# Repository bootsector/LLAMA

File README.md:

**LLAMA - Low Lag Amazing MiSTer Adapter**

This is an open-source / open-hardware controllers adapter for MiSTer FPGA.

Supported outputs are both USB (XInput) and MiSTer's [LLAPI](https://github.com/Kitrinx/LLAPI/blob/master/LLIO.sv) interface.

32U4 module designs include gerber files and SeeedStudio BOM file for Fusion
PCB Assembly service.

LLAMA currently supports original controllers for the systems below:

- Neo Geo / Neo Geo CD (**NOT compatible with SuperGun DB15 based controllers** )
- Super NES
- NES
- TurboGrafx-16 / PC Engine
- Sega Saturn
- Sega Genesis / Master System / Atari 2600 and compatibles

**Latency Measurements - 1000Hz USB polling mode**
| Controller | Samples | Average | Max     | Min   | Std Dev |
| ---------- | ------- | ------- | --------| ----- | ------- |
| LLAMA USB  | 2000    |1.6996ms |2.224ms  |1.188ms| 0.289ms

**Button Mapping**

It's possible to map buttons for each supported joystick. Button mapping is done
based on an index that maps to buttons of the internal abstract pad 
(XInput-like).

Mapping is fully customized by the user. Planning your mapping can be done with
the help of the mapper/LLAMA Mapping.xlsx spreadsheet. Change the buttons of
the supported pads in the "Input" area by selecting them from list boxes. You
can see how those mappings affect output for XInput (USB) and also LLAPI cores
by checking the "Output" area of the spreadsheet.

After setting the mappings in the spreadsheet, simply use the numbers inside
parenthesis for each button of each controller in the ```<profile>``` section of
the mapper/map.xml file. There are two profiles per controller. You just
apply the numbers at the same order they read from the spreadsheet to the
chosen controller profile.

After finishing the changes inside mapper/map.xml file, run the 
mapper/mapper.py application (tested only on Python 2.7). 

```
cd mapper
python mapper.py
```

You should probably
need to install intelhex package via pip beforehand.

```pip install intelhex```

The above will convert map.xml to a file named map.eep. This should be 
flashed into AVR's EEPROM like this:

```dfu-programmer atmega32u4 flash --eeprom map.eep --force```

Mapping is not mandatory. The firmware will save the defaults to EEPROM by
itself the first time it runs if no valid mapping/config is found.

Each controller has two mapping profiles. Below you can find the button
combination on each controller that will switch mapping profiles:

NeoGeo: Down + Start + B

NES: Down + Start + A

SNES: Down + Start + A

Saturn: Down + Start + C

TG16/PCE: Down + Start + I

Genesis: Down + Start + C

**Licensing:**

- Firmware and bootloader sources are licensed under [GPL-3.0](LICENSE)
- PCBs are licensed under [CC BY-NC-SA 4.0](pcb/LICENSE.txt)

**Disclaimer:**

The firmware source code made available here is an original creation by Bruno 
Freitas. 

The AVR ASM/C implementation of the LLAPI "slave" interface presented here
was created from scratch by Bruno Freitas. MiSTer's LLAPI "master" interface
protocol described [here](https://github.com/Kitrinx/LLAPI/blob/master/LLIO.sv) 
in SystemVerilog has been used as documentation and reference only.

No source code from third parties has been used used by this project.

No reverse-engineering has been done against commercial and non-commercial
products during the development of this project.

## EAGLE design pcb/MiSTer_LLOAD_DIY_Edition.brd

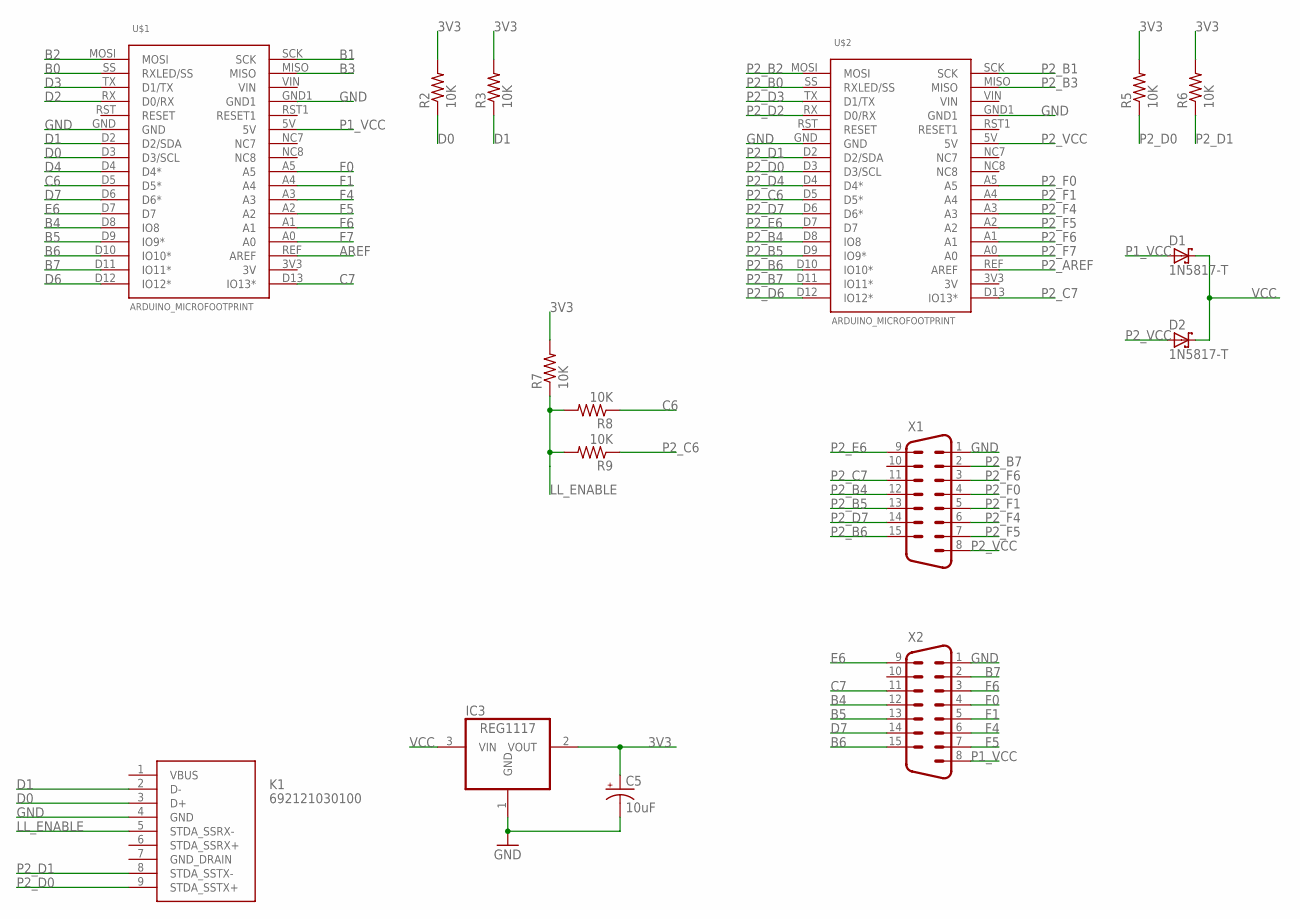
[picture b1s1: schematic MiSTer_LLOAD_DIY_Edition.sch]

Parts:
C5: 10uF; E2,5-6
D1, D2: 1N5817-T; DO41-7.6
IC3: REG1117; SOT223
K1: 692121030100
R2, R3, R5, R6, R7, R8, R9: 10K; 0207/10
U$1, U$2: ARDUINO_MICROFOOTPRINT; ARDUINO-MICRO
X1, X2: M15HP

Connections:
3V3: C5.+, IC3.2 (VOUT), R2.2, R3.2, R5.2, R6.2, R7.2
AREF: U$1.REF (AREF)
B0: U$1.SS (RXLED/SS)
B1: U$1.SCK
B2: U$1.MOSI
B3: U$1.MISO
B4: U$1.D8 (IO8), X2.12
B5: U$1.D9 (IO9*), X2.13
B6: U$1.D10 (IO10*), X2.15
B7: U$1.D11 (IO11*), X2.2
C6: R8.1, U$1.D5 (D5*)
C7: U$1.D13 (IO13*), X2.11
D0: K1.3 (D+), R2.1, U$1.D3 (D3/SCL)
D1: K1.2 (D-), R3.1, U$1.D2 (D2/SDA)
D2: U$1.RX (D0/RX)
D3: U$1.TX (D1/TX)
D4: U$1.D4 (D4*)
D6: U$1.D12 (IO12*)
D7: U$1.D6 (D6*), X2.14
E6: U$1.D7, X2.9
F0: U$1.A5, X2.4
F1: U$1.A4, X2.5
F4: U$1.A3, X2.6
F5: U$1.A2, X2.7
F6: U$1.A1, X2.3
F7: U$1.A0
GND: C5.-, IC3.1 (GND), K1.4 (GND), U$1.GND, U$1.GND1, U$2.GND, U$2.GND1, X1.1, X2.1
LL_ENABLE: K1.5 (STDA_SSRX-), R7.1, R8.2, R9.2
P1_VCC: D1.A, U$1.5V, X2.8
P2_AREF: U$2.REF (AREF)
P2_B0: U$2.SS (RXLED/SS)
P2_B1: U$2.SCK
P2_B2: U$2.MOSI
P2_B3: U$2.MISO
P2_B4: U$2.D8 (IO8), X1.12
P2_B5: U$2.D9 (IO9*), X1.13
P2_B6: U$2.D10 (IO10*), X1.15
P2_B7: U$2.D11 (IO11*), X1.2
P2_C6: R9.1, U$2.D5 (D5*)
P2_C7: U$2.D13 (IO13*), X1.11
P2_D0: K1.9 (STDA_SSTX+), R5.1, U$2.D3 (D3/SCL)
P2_D1: K1.8 (STDA_SSTX-), R6.1, U$2.D2 (D2/SDA)
P2_D2: U$2.RX (D0/RX)
P2_D3: U$2.TX (D1/TX)
P2_D4: U$2.D4 (D4*)
P2_D6: U$2.D12 (IO12*)
P2_D7: U$2.D6 (D6*), X1.14
P2_E6: U$2.D7, X1.9
P2_F0: U$2.A5, X1.4
P2_F1: U$2.A4, X1.5
P2_F4: U$2.A3, X1.6
P2_F5: U$2.A2, X1.7
P2_F6: U$2.A1, X1.3
P2_F7: U$2.A0
P2_VCC: D2.A, U$2.5V, X1.8
VCC: D1.C, D2.C, IC3.3 (VIN)

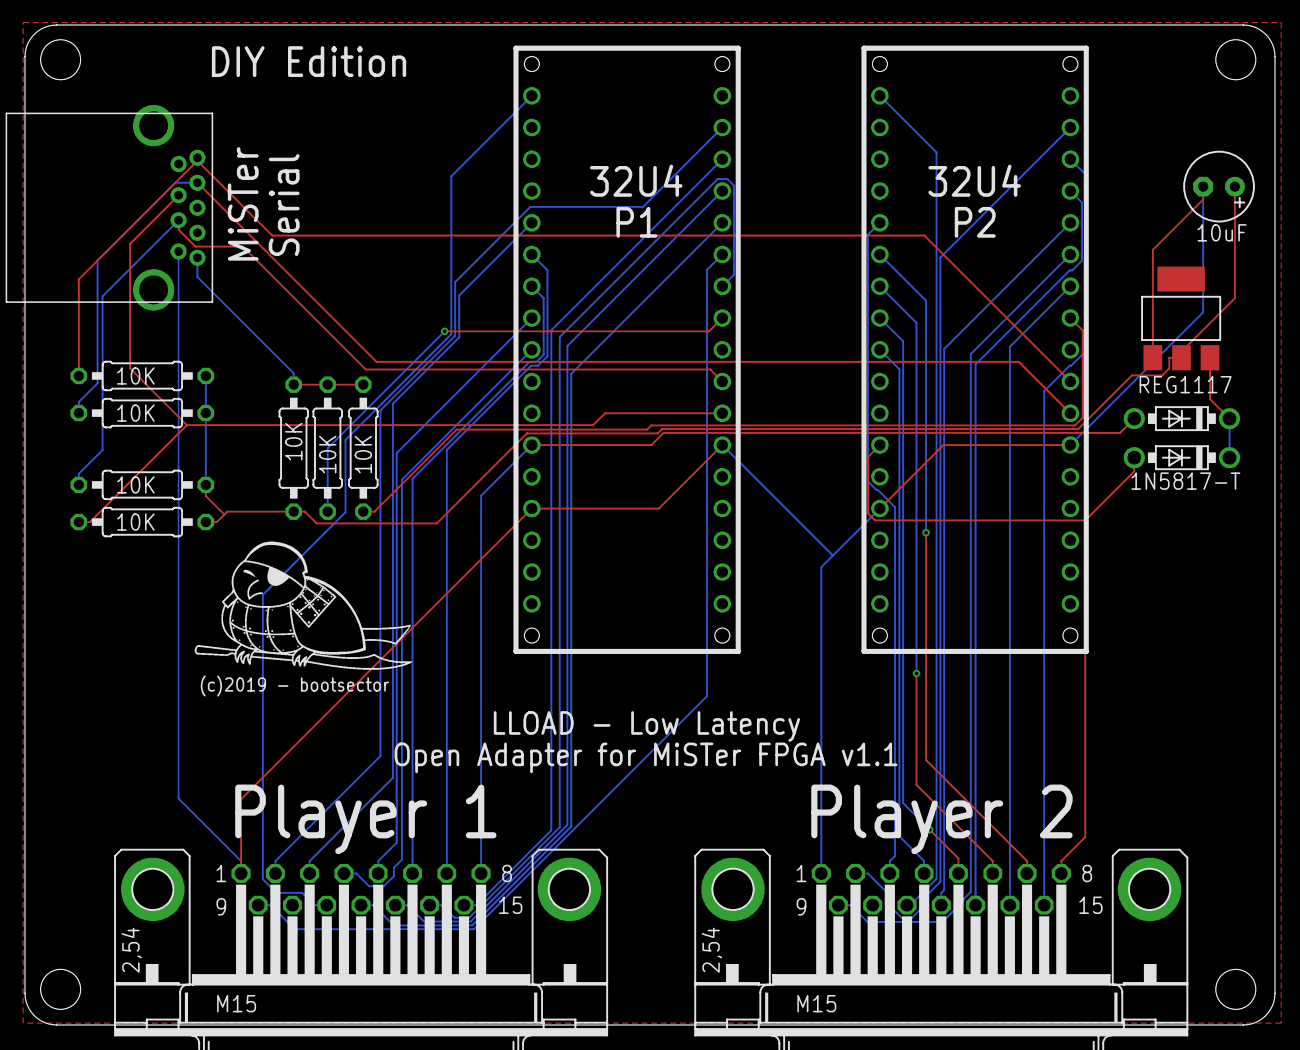
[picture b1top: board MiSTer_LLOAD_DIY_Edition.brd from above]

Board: 2 copper layers, 100.0 x 80.0 mm, 16 parts (0 on the bottom side), 36 nets.

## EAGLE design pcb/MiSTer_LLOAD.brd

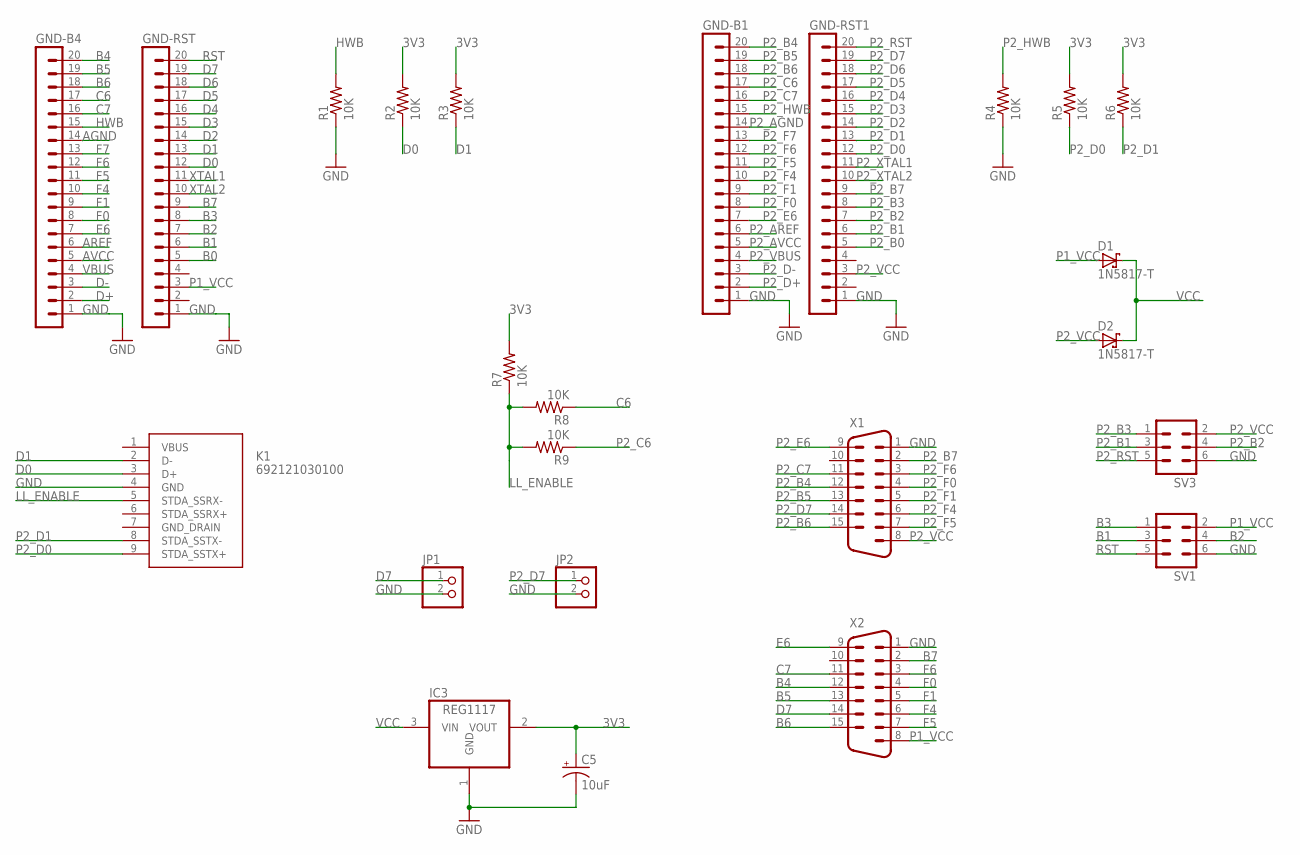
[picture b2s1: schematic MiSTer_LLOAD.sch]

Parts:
C5: 10uF; E2,5-6
D1, D2: 1N5817-T; DO41-7.6
GND-B1, GND-B4: MA20-1
GND-RST, GND-RST1: MA20-1
IC3: REG1117; SOT223
JP1, JP2: PINHD-1X2; 1X02
K1: 692121030100
R1, R2, R3, R4, R5, R6, R7, R8, R9: 10K; 0207/10
SV1, SV3: MA03-2
X1, X2: M15HP

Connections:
3V3: C5.+, IC3.2 (VOUT), R2.2, R3.2, R5.2, R6.2, R7.2
AGND: GND-B4.14
AREF: GND-B4.6
AVCC: GND-B4.5
B0: GND-RST.5
B1: GND-RST.6, SV1.3
B2: GND-RST.7, SV1.4
B3: GND-RST.8, SV1.1
B4: GND-B4.20, X2.12
B5: GND-B4.19, X2.13
B6: GND-B4.18, X2.15
B7: GND-RST.9, X2.2
C6: GND-B4.17, R8.1
C7: GND-B4.16, X2.11
D0: GND-RST.12, K1.3 (D+), R2.1
D1: GND-RST.13, K1.2 (D-), R3.1
D2: GND-RST.14
D3: GND-RST.15
D4: GND-RST.16
D5: GND-RST.17
D6: GND-RST.18
D7: GND-RST.19, JP1.1, X2.14
D+: GND-B4.2
D-: GND-B4.3
E6: GND-B4.7, X2.9
F0: GND-B4.8, X2.4
F1: GND-B4.9, X2.5
F4: GND-B4.10, X2.6
F5: GND-B4.11, X2.7
F6: GND-B4.12, X2.3
F7: GND-B4.13
GND: C5.-, GND-B1.1, GND-B4.1, GND-RST.1, GND-RST1.1, IC3.1 (GND), JP1.2, JP2.2, K1.4 (GND), R1.1, R4.1, SV1.6, SV3.6, X1.1, X2.1
HWB: GND-B4.15, R1.2
LL_ENABLE: K1.5 (STDA_SSRX-), R7.1, R8.2, R9.2
P1_VCC: D1.A, GND-RST.3, SV1.2, X2.8
P2_AGND: GND-B1.14
P2_AREF: GND-B1.6
P2_AVCC: GND-B1.5
P2_B0: GND-RST1.5
P2_B1: GND-RST1.6, SV3.3
P2_B2: GND-RST1.7, SV3.4
P2_B3: GND-RST1.8, SV3.1
P2_B4: GND-B1.20, X1.12
P2_B5: GND-B1.19, X1.13
P2_B6: GND-B1.18, X1.15
P2_B7: GND-RST1.9, X1.2
P2_C6: GND-B1.17, R9.1
P2_C7: GND-B1.16, X1.11
P2_D0: GND-RST1.12, K1.9 (STDA_SSTX+), R5.1
P2_D1: GND-RST1.13, K1.8 (STDA_SSTX-), R6.1
P2_D2: GND-RST1.14
P2_D3: GND-RST1.15
P2_D4: GND-RST1.16
P2_D5: GND-RST1.17
P2_D6: GND-RST1.18
P2_D7: GND-RST1.19, JP2.1, X1.14
P2_D+: GND-B1.2
P2_D-: GND-B1.3
P2_E6: GND-B1.7, X1.9
P2_F0: GND-B1.8, X1.4
P2_F1: GND-B1.9, X1.5
P2_F4: GND-B1.10, X1.6
P2_F5: GND-B1.11, X1.7
P2_F6: GND-B1.12, X1.3
P2_F7: GND-B1.13
P2_HWB: GND-B1.15, R4.2
P2_RST: GND-RST1.20, SV3.5
P2_VBUS: GND-B1.4
P2_VCC: D2.A, GND-RST1.3, SV3.2, X1.8
P2_XTAL1: GND-RST1.11
P2_XTAL2: GND-RST1.10
RST: GND-RST.20, SV1.5
VBUS: GND-B4.4
VCC: D1.C, D2.C, IC3.3 (VIN)
XTAL1: GND-RST.11
XTAL2: GND-RST.10

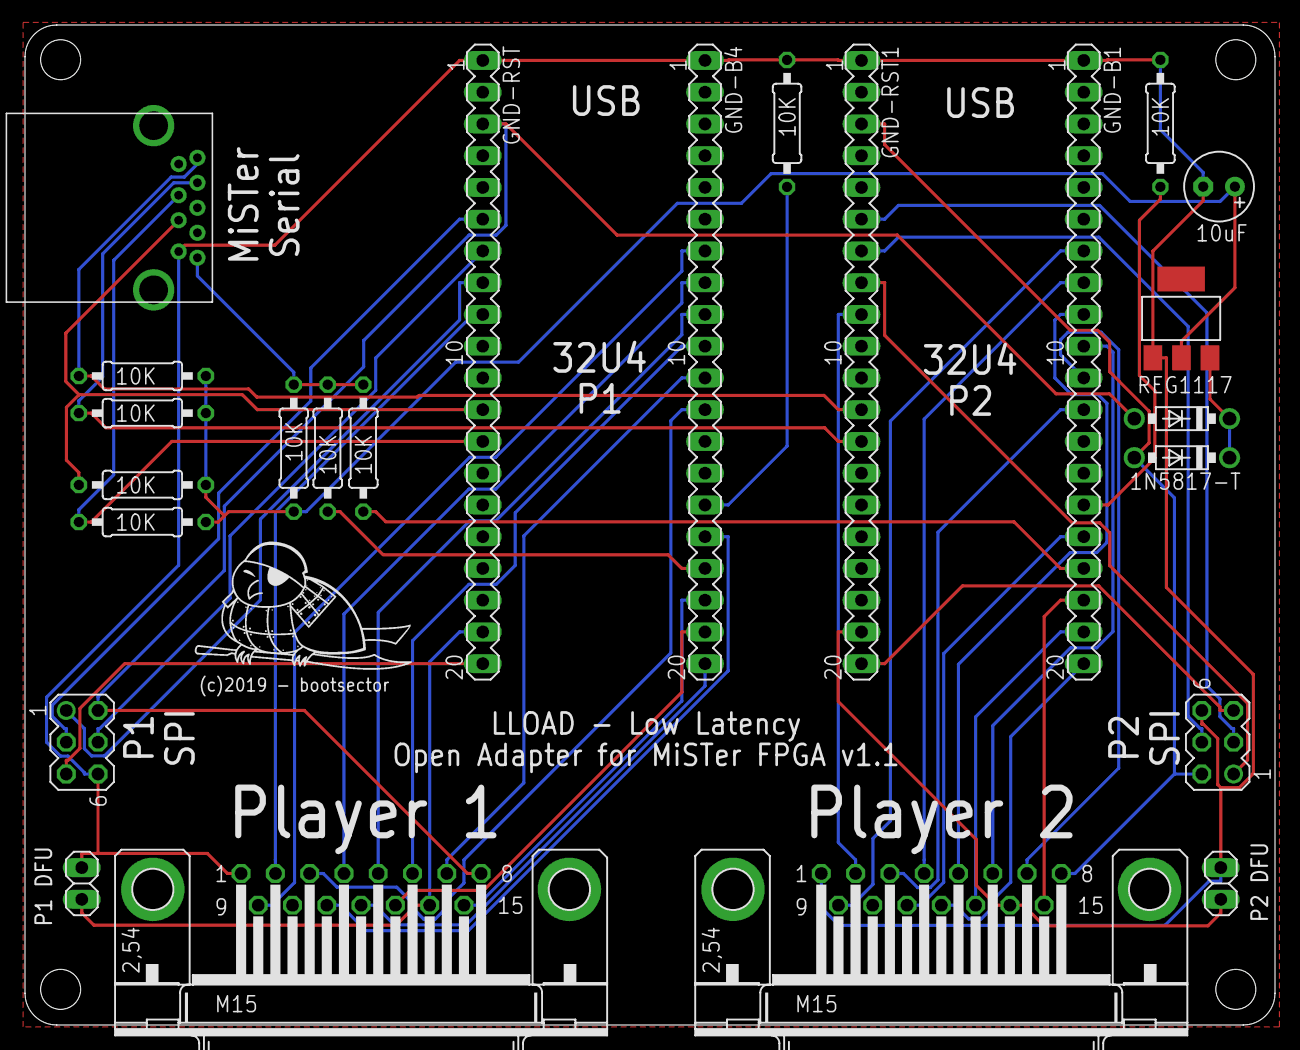
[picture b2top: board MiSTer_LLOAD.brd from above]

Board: 2 copper layers, 100.0 x 80.0 mm, 24 parts (0 on the bottom side), 46 nets.

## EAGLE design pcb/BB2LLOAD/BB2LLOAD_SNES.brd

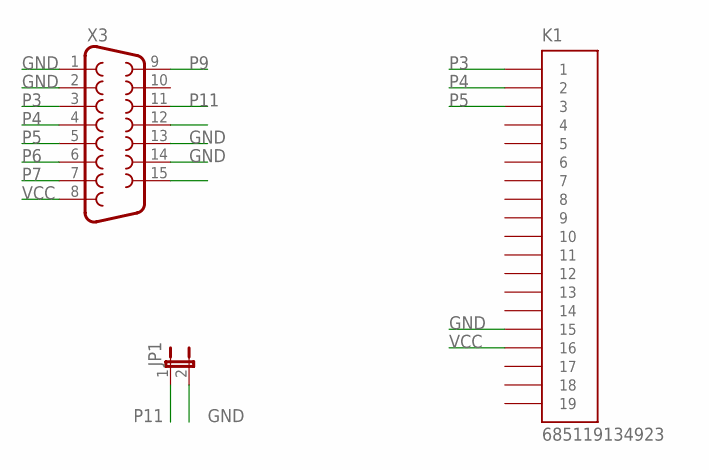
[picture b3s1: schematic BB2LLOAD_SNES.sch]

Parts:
JP1: JP1E; JP1
K1: 685119134923
X3: F15HP

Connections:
GND: JP1.2, K1.15, X3.1, X3.2, X3.13, X3.14
P3: K1.1, X3.3
P4: K1.2, X3.4
P5: K1.3, X3.5
P6: X3.6
P7: X3.7
P9: X3.9
P11: JP1.1, X3.11
VCC: K1.16, X3.8

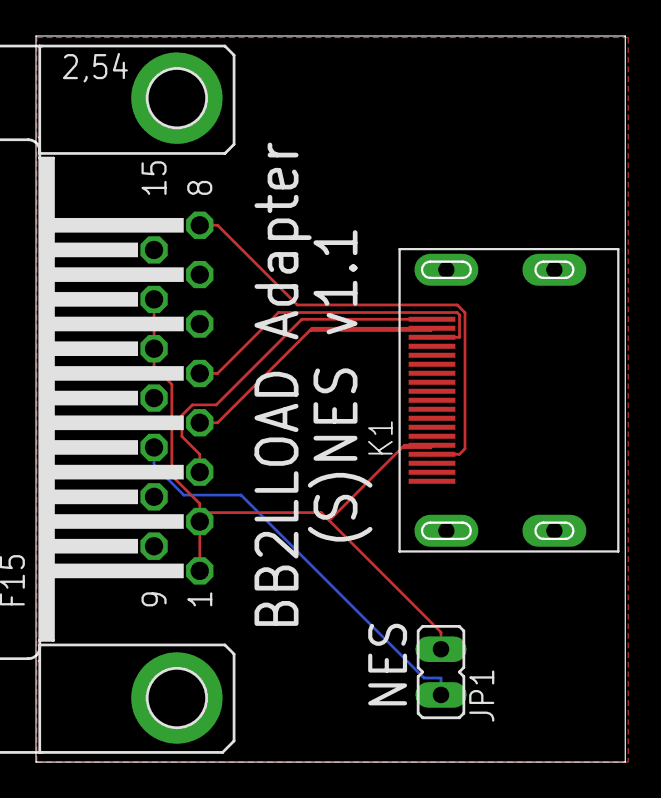
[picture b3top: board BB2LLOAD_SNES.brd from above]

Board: 2 copper layers, 32.6 x 40.2 mm, 3 parts (0 on the bottom side), 6 nets.

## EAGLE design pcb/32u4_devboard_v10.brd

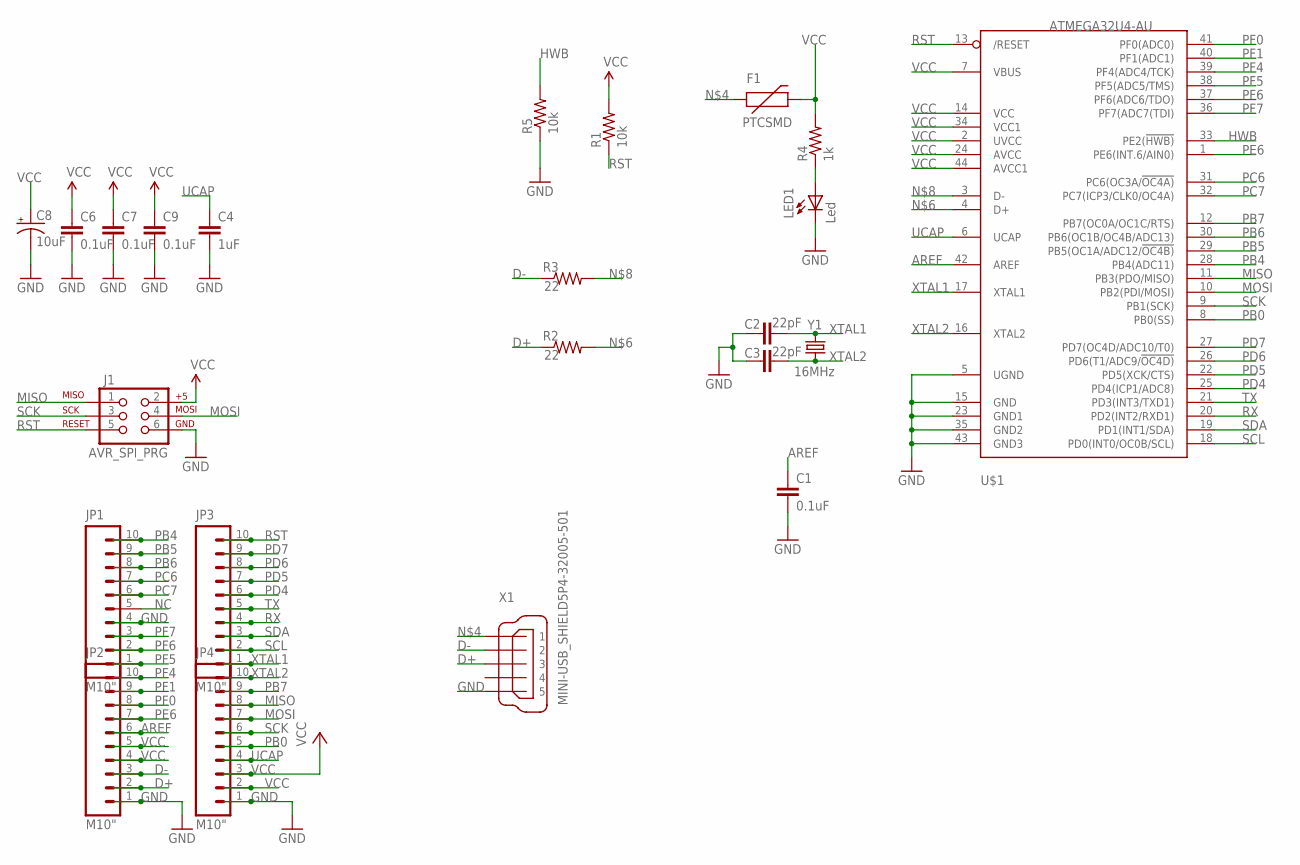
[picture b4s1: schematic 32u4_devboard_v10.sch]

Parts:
C1, C6, C7, C9: 0.1uF; 0805
C2, C3: 22pF; 0603-CAP
C4: 1uF; 0805
C8: 10uF; EIA3216
F1: PTCSMD; PTC-1206
J1: AVR_SPI_PRG; 2X3
JP1, JP2, JP3, JP4: M10"; 1X10
LED1: Led; CHIP-LED0805
R1, R5: 10k; 0805
R2, R3: 22; 0805
R4: 1k; 0805
U$1: ATMEGA32U4-AU; TQFP44
X1: MINI-USB_SHIELD5P4-32005-501; 32005-501
Y1: 16MHz; HC49US

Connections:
AREF: C1.1, JP2.6, U$1.42 (AREF)
D+: JP2.2, R2.1, X1.3
D-: JP2.3, R3.1, X1.2
GND: C1.2, C2.1, C3.1, C4.2, C6.2, C7.2, C8.C (-), C9.2, J1.6, JP1.4, JP2.1, JP4.1, LED1.C, R5.1, U$1.5 (UGND), U$1.15 (GND), U$1.23 (GND1), U$1.35 (GND2), U$1.43 (GND3), X1.5
HWB: R5.2, U$1.33 (PE2(!HWB))
MISO: J1.1, JP4.8, U$1.11 (PB3(PDO/MISO))
MOSI: J1.4, JP4.7, U$1.10 (PB2(PDI/MOSI))
unnamed: F1.1, X1.1
unnamed: R2.2, U$1.4 (D+)
unnamed: R3.2, U$1.3 (D-)
unnamed: LED1.A, R4.1
NC: JP1.5
PB0: JP4.5, U$1.8 (PB0(SS))
PB4: JP1.10, U$1.28 (PB4(ADC11))
PB5: JP1.9, U$1.29 (PB5(OC1A/ADC12/!OC4B))
PB6: JP1.8, U$1.30 (PB6(OC1B/OC4B/ADC13))
PB7: JP4.9, U$1.12 (PB7(OC0A/OC1C/RTS))
PC6: JP1.7, U$1.31 (PC6(OC3A/!OC4A))
PC7: JP1.6, U$1.32 (PC7(ICP3/CLK0/OC4A))
PD4: JP3.6, U$1.25 (PD4(ICP1/ADC8))
PD5: JP3.7, U$1.22 (PD5(XCK/CTS))
PD6: JP3.8, U$1.26 (PD6(T1/ADC9/!OC4D))
PD7: JP3.9, U$1.27 (PD7(OC4D/ADC10/T0))
PE6: JP2.7, U$1.1 (PE6(INT.6/AIN0))
PF0: JP2.8, U$1.41 (PF0(ADC0))
PF1: JP2.9, U$1.40 (PF1(ADC1))
PF4: JP2.10, U$1.39 (PF4(ADC4/TCK))
PF5: JP1.1, U$1.38 (PF5(ADC5/TMS))
PF6: JP1.2, U$1.37 (PF6(ADC6/TDO))
PF7: JP1.3, U$1.36 (PF7(ADC7(TDI))
RST: J1.5, JP3.10, R1.1, U$1.13 (/RESET)
RX: JP3.4, U$1.20 (PD2(INT2/RXD1))
SCK: J1.3, JP4.6, U$1.9 (PB1(SCK))
SCL: JP3.2, U$1.18 (PD0(INT0/OC0B/SCL))
SDA: JP3.3, U$1.19 (PD1(INT1/SDA))
TX: JP3.5, U$1.21 (PD3(INT3/TXD1))
UCAP: C4.1, JP4.4, U$1.6 (UCAP)
VCC: C6.1, C7.1, C8.A (+), C9.1, F1.2, J1.2, JP2.4, JP2.5, JP4.2, JP4.3, R1.2, R4.2, U$1.2 (UVCC), U$1.7 (VBUS), U$1.14 (VCC), U$1.24 (AVCC), U$1.34 (VCC1), U$1.44 (AVCC1)
XTAL1: C2.2, JP3.1, U$1.17 (XTAL1), Y1.2
XTAL2: C3.2, JP4.10, U$1.16 (XTAL2), Y1.1

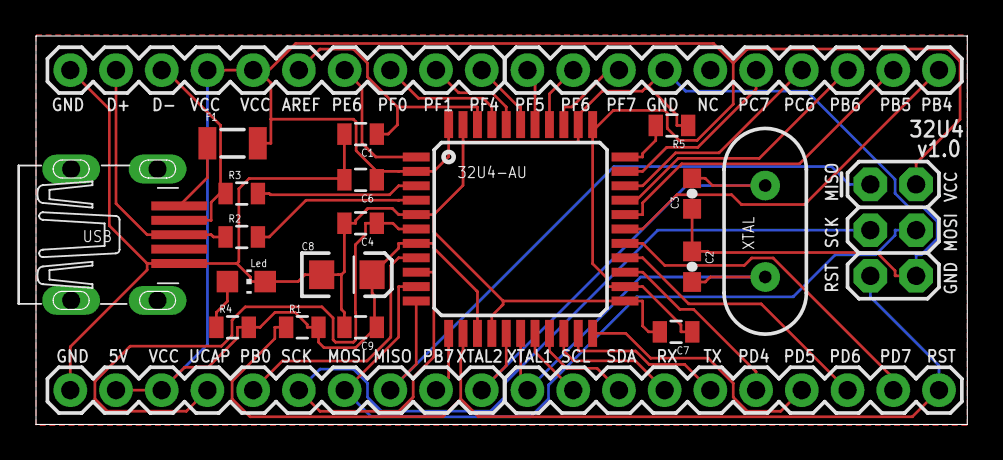
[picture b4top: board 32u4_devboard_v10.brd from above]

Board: 2 copper layers, 51.7 x 21.6 mm, 23 parts (0 on the bottom side), 39 nets.

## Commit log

2019-09-30 Adding .gitignore
2019-10-01 Corrected LLIO data polling pin
2019-10-01 Corrected LLIO polling command
2019-10-03 Inverting LLIO received command data bits
2019-10-06 Corrected ISR overhead number of cycles (4 -> 7) as per datasheet. Prioritize LL processing over USB
2019-10-07 Put LL registers and buffers in a clean state if LL is not enabled.
2019-10-07 Include files fix
2019-10-08 Defining ID bits for supported pads on DB15
2019-10-08 Auto input detection framework
2019-10-08 Adding pad reading drivers and input cables schematics
2019-10-08 Adding some LLAPI MiSTer cores rbf files
2019-10-09 Polling command is 0x01 and not 0x10 as per https://github.com/Kitrinx/LLAPI/blob/a9e8d0d8a6ad6cdb0262cdd70c30f7aff7388922/LLIO.sv#L121
2019-10-09 Update readme and licensing
2019-10-09 README markup fixes
2019-10-09 Attribution added to LLIO module files
2019-10-09 LLIO module files disclaimer reformatting
2019-10-09 LLIO module files disclaimer kept original from Kitrinx work (MIT License). This project's more restrictive license gets precedence (GPL-v3.0).
2019-10-09 Talked to Kitrinx and she told me that since I didn't use any portions of her code, I shouldn't add her licensing header. That makes sense to me. Reverting.
2019-10-10 Linking to LLAPI's MiSTer source code in the README
2019-10-10 Adding Disclaimer section in the README
2019-10-10 README changes
2019-10-10 Removing unecessary LLAPI rbf cores. These can be downloaded from https://github.com/MiSTer-LLAPI/
2019-10-12 Adding BB2LLOAD pcb files for Saturn
2019-10-12 Changed form factor of the bb2load pcb (slim)
2019-10-12 Adding bb2lload pcbs for (s)nes cables.
2019-10-12 Adding bb2lload pcbs for TG16 cables.
2019-10-12 Adding DB9 to DB15 adapter pcb files
2019-10-12 LL detection pin setup fix
2019-10-12 LLIO response to cmd 0x00 fix
2019-10-13 Fixing DB9 adapter ID bits
2019-10-14 Proto v0.3 PCB - It does not rely on Serial IO VCC anymore
2019-10-14 Needs to pull both latch and data low as a response to 0x00????
2019-10-15 LLIO timing calibration
2019-10-15 LLIO output tweaks
2019-10-15 Small LLIO refactoring
2019-10-15 LLAPI uses HAT for D-Pad
2019-10-15 Oops!
2019-10-15 Adding support for LLAPI HOME key
2019-10-15 LLAPI is alive and kicking! :D
2019-10-15 Added synchronized pad reading when in LLAPI mode
2019-10-16 Removing dependency of LLIO reading callback from Output_Init
2019-10-16 Promoting LLOAD PCB to v1.0
2019-10-17 Optimizing output buffers clear: Now it happens only during output mode switches (LL/USB)
2019-10-17 Added DIY (Arduino Micro based) PCB edition. Untested!
2019-10-19 Adding support for OSD triggering via USB in LLAPI mode until LLAPI supports this natively
2019-10-29 Changing CALL to RCALL - AVR assembler is already doing this as part of -mrelax flag
2019-11-06 Undefining USB device serial number so MiSTer does not get crazy
2019-11-06 Revert "Undefining USB device serial number so MiSTer does not get crazy"
    This reverts commit 8516f9a6f194a1c2c52c805fb26148e81404ed00.
2019-11-06 Adding acrilic case cut fie
2019-11-26 Removed alternate VCC (3.3v) from DB15 pin 10. This will not make it directly compatible with supergun input, but at least no harm will be done in case someone inadvertently uses a supergun with it. 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
2019-12-09 Update README.md: supported controllers
2020-01-26 Added missing XInput LT and RT translations
2020-01-26 Update Saturn_In.c
    Introduces the changes mentioned by Ulao to increase saturn controller compatibility to 3rd parties and retro-bit.
    This does not work with my retro-bit wireless receiver but does not break compatibility with my existing OEM controller either
    // Reading L
    // Reading Up, Down, Left, Right
    // Reading B, C, A and Start
    // Reading Z, Y, X and R
2020-02-13 Reporting correct pad id to LLAPI host
2020-02-13 Releases
    P1 and P2 are the same firmware using different PIDs respectively
2020-02-13 Revert "Releases"
    This reverts commit ccb45df2201fa646f745fa50ab8c17ac86678e91.
2020-02-13 Revert "Merge remote-tracking branch 'upstream/master'"
    This reverts commit 8ec29b8f08082a58d228766d61c6eb5b501eb627, reversing
    changes made to be25cc6d00a0c75a74cd8cf2fe1c65df2dd6be01.
2020-02-13 Revert "Reporting correct pad id to LLAPI host"
    This reverts commit 4b047ea8b23090d3679b640455e2e45e9ea80044.
2020-02-14 Corrected TG16 Avenue6 -> SNES mapping: IV V VI III II I -> L X R Y B A
2020-02-17 Trying to make it work on retrobit Saturn pad
2020-02-18 Adding pad detection routine
2020-02-19 Fixed inverting ID bits
2020-03-03 Adding button mapping support
2020-03-03 Adding support to two mapping profiles per input controller
2020-03-04 Fixed mapping table inside config struct
2020-03-04 Added LLOAD Mapping spreadsheet tool.
2020-03-04 Unfrozen spreadsheet panes
2020-03-04 Correcting map change info.
2020-03-04 Simplified map profile rotation debouncing
2020-03-05 Updated mapping information inside README
2020-03-05 Fix typo and markup for xml tag
2020-03-05 Sync mapping with pad reads
2020-03-05 Let us avoid duplicate code
2020-03-06 Adding xml map file with alternate profile (1) for SNES, Genesis and Saturn pads
2020-03-06 Making alternative map profiles (1) for SNES, Genesis and Saturn as defaults for initial EEPROM config
2020-03-06 Correcting comment about LLAPI and OSD trigger
2020-03-06 Removing unecessary variable
2020-03-07 Turned on O3 avr-gcc flag (speed optimization) for button mapper routine
2020-03-09 Map switching combo now takes in three buttons
2020-03-09 Fix README.md
2020-04-02 Start renaming project to LLAMA
2020-04-15 Add latency measurements
2020-04-15 name change
2020-04-15 Latency measurements - Specify 1000Hz USB polling mode
2020-07-14 Disabled pull-ups for TG16/PCE controllers as those were interfering with the controller internal ones (6 button ones mainly). Also, decreased controller polling frequency.
2021-12-06 Add support to supergun adapter

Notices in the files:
pcb/MiSTer_LLOAD.brd:
(c)2019 - bootsector
parts and their libraries:
wuerth: Copyright: Würth Elektronik
